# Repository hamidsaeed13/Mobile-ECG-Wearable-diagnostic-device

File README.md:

# Mobile ECG Project

### Supervisor:
-Prof. Dr. Shahid Khattak

### Team Members:
- Abdul Hameed
- M. Hamid Saeed
- Mujahid Haider

---

## Introduction:
This project aims to create a healthcare wearable Clinical Grade ECG device for continuous heart monitoring.

## Motivation:
- Existing ECG solutions are large and costly.
- Patients must be hospitalized, making it difficult to maintain long-term ECG logs.
- 24/7 ECG monitoring in remote areas is a challenge.

## Our Solution:
- 10-lead, 12-channel ECG diagnostic device.
- Bluetooth-enabled data transmission to smartphones for processing and log maintenance.
 
|  |  |

---

## Aims and Objectives:
- Signal acquisition and conditioning.
- Multiplexing and Bluetooth communication.
- Real-time ECG graph visualization.
- Log maintenance and record-sharing with cardiologists.

---

## System Block Diagram:

---
## Our Project:

---
## Filter Design:
- **Schematic**: 
  - R1 = 142.1KΩ
  - R2 = 120KΩ
  - C1 = C2 = 10nF
- **Design**: 
- **PCB**: 

---

## ADS1298:
- **Breakout Board**: 

- **PCB Layout**: 

---

## Android Application:
- Features:
  - Navigation menu with user details, doctor communication, and log maintenance.
  - 12-channel ECG view, Bluetooth connection, and real-time communication.
  - Options to find doctors and maintain a patient history.

---
## Database

---

## Working Schedule:
- Phase I (March 2016 - May 2016)
- Phase II (August 2016 - Onwards)

---

## Questions:
Feel free to reach out for further details.
*contact*: +92301 2216201
email: hamidsaeed13@gmail.com

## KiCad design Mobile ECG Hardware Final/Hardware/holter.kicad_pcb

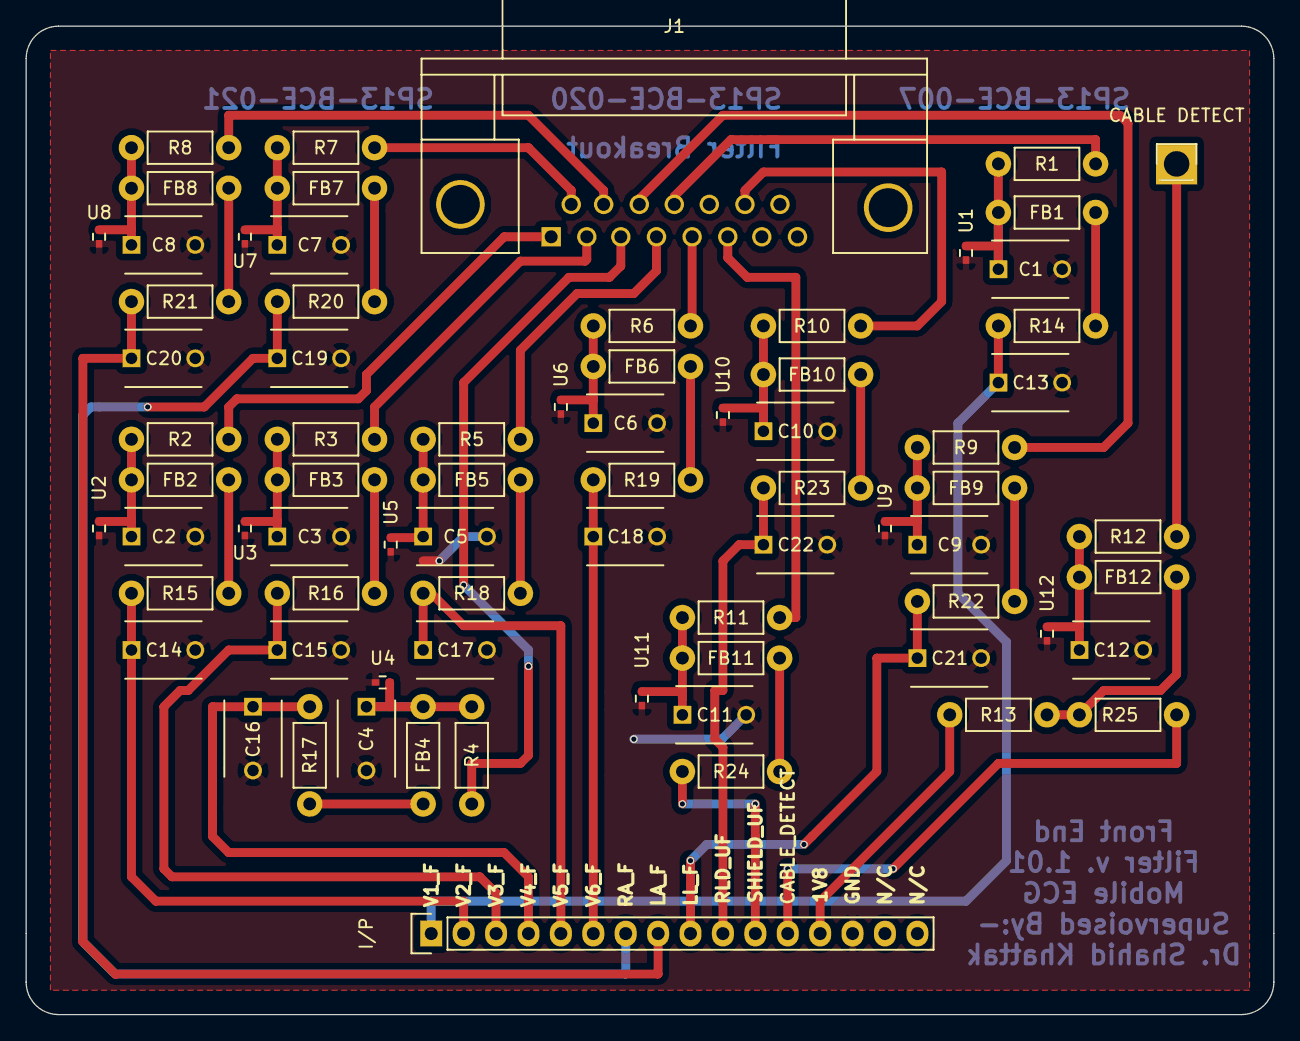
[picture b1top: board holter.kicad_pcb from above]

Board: 2 copper layers, 97.8 x 77.5 mm, 74 parts (0 on the bottom side), 50 nets.

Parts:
C1, C2, C3, C4, C5, C6, C7, C8, C9, C10, C11, C12, C13, C14, C15, C16, C17, C18, C19, C20, C21, C22: 47pF; C_Disc_D6_P5
CABLE DETECT: CONN_01X01; Pin_Header_Straight_1x01
FB1, FB2, FB3, FB4, FB5, FB6, FB7, FB8, FB9, FB10, FB11, FB12: FILTER; Resistor_Horizontal_RM7mm
I/P: CONN_01X16; Pin_Header_Straight_1x16
J1: DB15; DB15FC
R1, R2, R3, R4, R5, R6, R7, R8, R9, R10, R11, R12, R24: 470; Resistor_Horizontal_RM7mm
R13: 100k; Resistor_Horizontal_RM7mm
R14, R15, R16, R17, R18, R19, R20, R21, R22, R23: 10k; Resistor_Horizontal_RM7mm
R25: 47k; Resistor_Horizontal_RM7mm
U1, U2, U3, U4, U5, U6, U7, U8, U9, U10, U11, U12: TPD1E10B06DPYR; C_0402

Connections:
+1V8: I/P.13, R13.1
CABLE_DETECT: I/P.12, R25.2
DETECT: CABLE DETECT.1, R12.2
GND: C1.2, C2.2, C3.2, C4.2, C5.2, C6.2, C7.2, C8.2, C9.2, C10.2, C11.2, C12.2, C13.2, C14.2, C15.2, C16.2, C17.2, C18.2, C19.2, C20.2, C21.2, C22.2, I/P.14, U1.2, U2.2, U3.2, U4.2, U5.2, U6.2, U7.2, U8.2, U9.2, U10.2, U11.2, U12.2
LA: J1.10, R8.2
LA_F: C20.1, I/P.8, R21.1
LL: J1.11, R9.2
LL_F: C21.1, I/P.9, R22.1
unnamed: C1.1, FB1.1, R1.1, U1.1
unnamed: C2.1, FB2.1, R2.1, U2.1
unnamed: C3.1, FB3.1, R3.1, U3.1
unnamed: C4.1, FB4.1, R4.1, U4.1
unnamed: C5.1, FB5.1, R5.1, U5.1
unnamed: C6.1, FB6.1, R6.1, U6.1
unnamed: C7.1, FB7.1, R7.1, U7.1
unnamed: C8.1, FB8.1, R8.1, U8.1
unnamed: C9.1, FB9.1, R9.1, U9.1
unnamed: C10.1, FB10.1, R10.1, U10.1
unnamed: C11.1, FB11.1, R11.1, U11.1
unnamed: C12.1, FB12.2, R12.1, U12.1
unnamed: FB1.2, R14.2
unnamed: FB2.2, R15.2
unnamed: FB3.2, R16.2
unnamed: FB4.2, R17.2
unnamed: FB5.2, R18.2
unnamed: FB6.2, R19.2
unnamed: FB7.2, R20.2
unnamed: FB8.2, R21.2
unnamed: FB9.2, R22.2
unnamed: FB10.2, R23.2
unnamed: FB11.2, R24.2
unnamed: FB12.1, R13.2, R25.1
RA: J1.9, R7.2
RA_F: C19.1, I/P.7, R20.1
RLD: J1.14, R10.2
RLD_UF: C22.1, I/P.10, R23.1
SHIELD: J1.6, R11.2
SHIELD_UF: I/P.11, R24.1
V1: J1.12, R1.2
V1_F: C13.1, I/P.1, R14.1
V2: J1.1, R2.2
V2_F: C14.1, I/P.2, R15.1
V3: J1.2, R3.2
V3_F: C15.1, I/P.3, R16.1
V4: J1.3, R4.2
V4_F: C16.1, I/P.4, R17.1
V5: J1.4, R5.2
V5_F: C17.1, I/P.5, R18.1
V6: J1.5, R6.2
V6_F: C18.1, I/P.6, R19.1

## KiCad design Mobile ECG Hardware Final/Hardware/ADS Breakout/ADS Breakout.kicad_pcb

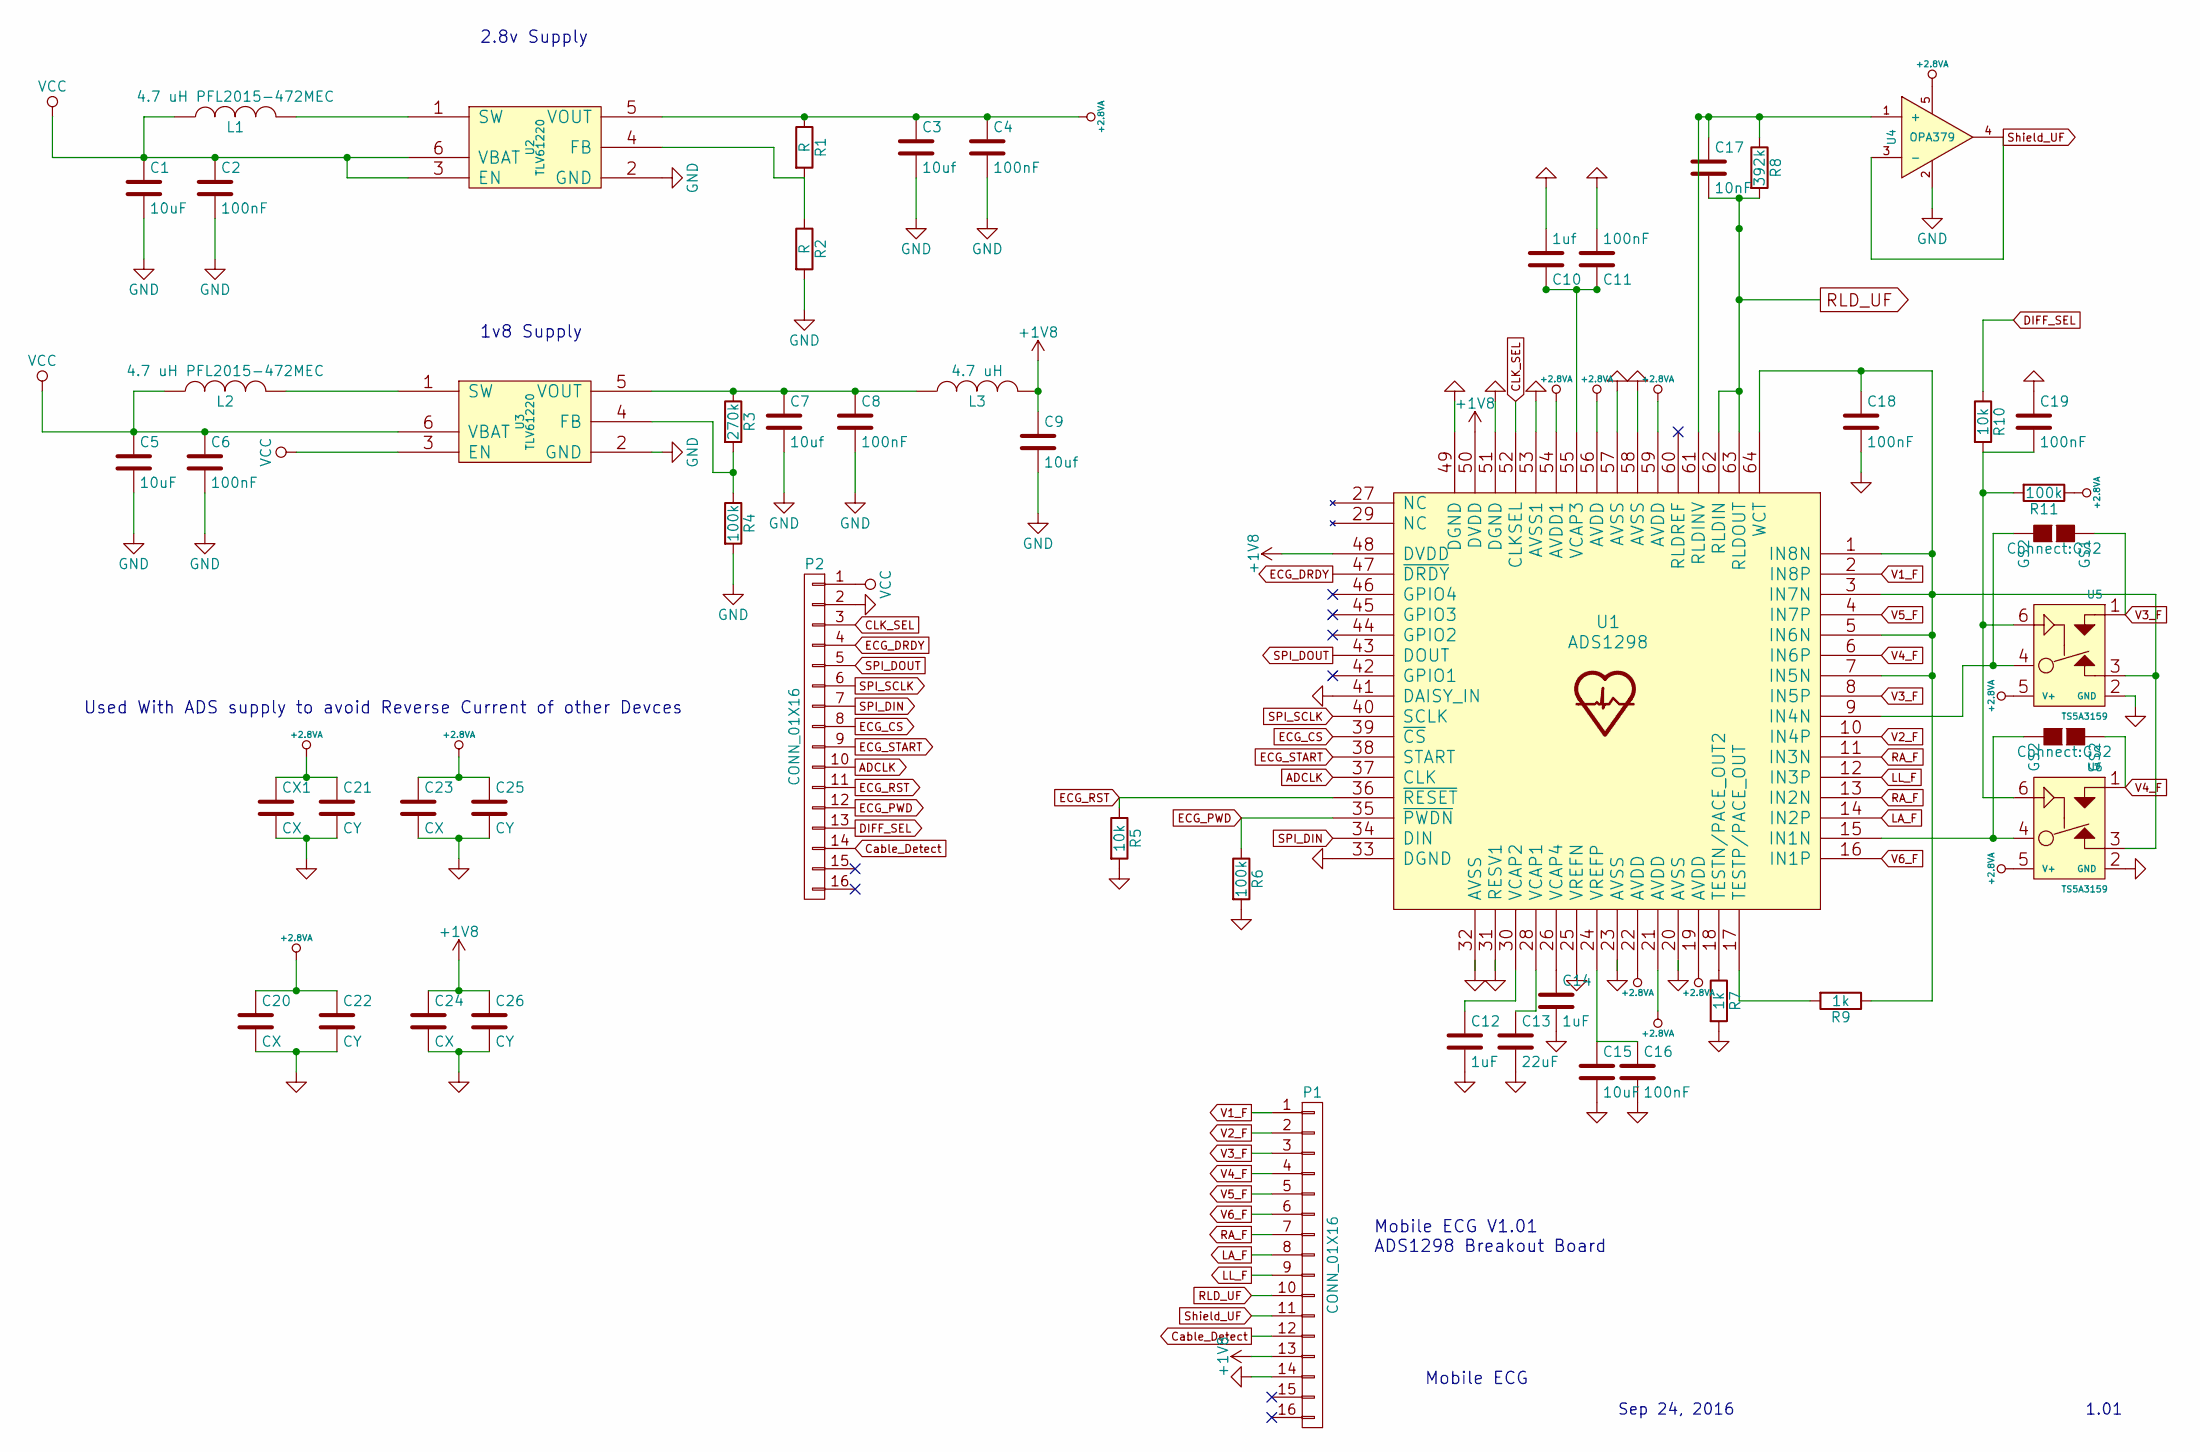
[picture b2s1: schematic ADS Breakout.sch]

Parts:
C1, C5, C15: 10uF; C_Disc_D3_P2.5
C2, C4, C6, C8, C11, C16, C18, C19: 100nF; C_Disc_D3_P2.5
C3, C7, C9: 10uf; C_Disc_D3_P2.5
C10: 1uf; C_Disc_D3_P2.5
C12, C14: 1uF; C_Disc_D3_P2.5
C13: 22uF; C_Disc_D3_P2.5
C17: 10nF; C_Disc_D3_P2.5
C20, C23, C24: CX; C_Disc_D3_P2.5
C21, C22, C25, C26: CY; C_Disc_D3_P2.5
CX1: CX; C_Disc_D3_P2.5
GS1, GS2: GS2
L1, L2: 4.7 uH PFL2015-472MEC; Resistor_Horizontal_RM7mm
L3: 4.7 uH; Resistor_Horizontal_RM7mm
P1, P2: CONN_01X16; Pin_Header_Straight_1x16
R1, R2: R; Resistor_Horizontal_RM7mm
R3: 270k; Resistor_Horizontal_RM7mm
R4, R6, R11: 100k; Resistor_Horizontal_RM7mm
R5, R10: 10k; Resistor_Horizontal_RM7mm
R7, R9: 1k; Resistor_Horizontal_RM7mm
R8: 392k; Resistor_Horizontal_RM7mm
U1: ADS1298; TQFP-64_10x10mm_Pitch0.5mm
U2, U3: TLV61220; SOT-23-6
U4: OPA379; SC-70-5
U5, U6: TS5A3159; SOT-23-6

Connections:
+1V8: C9.1, C24.1, C26.1, L3.2, P1.13, U1.48 (DVDD), U1.50 (DVDD); also elsewhere on the board
+2.8VA: C3.1, C4.1, C20.1, C21.1, C22.1, C23.1, C25.1, CX1.1, R1.1, R11.1, U1.19 (AVDD), U1.21 (AVDD), U1.22 (AVDD), U1.54 (AVDD1), U1.56 (AVDD), U1.59 (AVDD), U2.5 (VOUT), U4.5, U5.5 (V+), U6.5 (V+)
ADCLK: P2.10, U1.37 (CLK); also elsewhere on the board
CLK_SEL: P2.3, U1.52 (CLKSEL); also elsewhere on the board
DIFF_SEL: P2.13, R10.1; also elsewhere on the board
ECG_CS: P2.8, U1.39 (~CS); also elsewhere on the board
ECG_DRDY: P2.4, U1.47 (~DRDY); also elsewhere on the board
ECG_PWD: P2.12, R6.1, U1.35 (~PWDN); also elsewhere on the board
ECG_RST: P2.11, R5.1, U1.36 (~RESET); also elsewhere on the board
ECG_START: P2.9, U1.38 (START); also elsewhere on the board
GND: C1.2, C2.2, C3.2, C4.2, C5.2, C6.2, C7.2, C8.2, C9.2, C10.2, C11.2, C12.2, C13.2, C14.2, C15.2, C16.2, C18.2, C19.1, C20.2, C21.2, C22.2, C23.2, C24.2, C25.2, C26.2, CX1.2, P1.14, P2.2, R2.2, R4.2, R5.2, R6.2, R7.2, U1.20 (AVSS), U1.23 (AVSS), U1.25 (VREFN), U1.31 (RESV1), U1.32 (AVSS), U1.33 (DGND), U1.41 (DAISY_IN), U1.49 (DGND), U1.51 (DGND), U1.53 (AVSS1), U1.57 (AVSS), U1.58 (AVSS), U2.2 (GND), U3.2 (GND), U4.2, U5.2 (GND), U6.2 (GND); also elsewhere on the board
LA_F: P1.8, U1.14 (IN2P); also elsewhere on the board
LL_F: P1.9, U1.12 (IN3P); also elsewhere on the board
unnamed: C7.1, C8.1, L3.1, R3.1, U3.5 (VOUT)
unnamed: C10.1, C11.1, U1.55 (VCAP3)
unnamed: C12.1, U1.30 (VCAP2)
unnamed: C13.1, U1.28 (VCAP1)
unnamed: C14.1, U1.26 (VCAP4)
unnamed: C15.1, C16.1, U1.24 (VREFP)
unnamed: C17.1, R8.1, U1.61 (RLDINV), U4.1 (+)
unnamed: C18.1, R9.1, U1.1 (IN8N), U1.3 (IN7N), U1.5 (IN6N), U1.7 (IN5N), U1.64 (WCT), U5.3, U6.3
unnamed: C19.2, R10.2, R11.2, U5.6, U6.6
unnamed: GS1.2 (G2), U1.9 (IN4N), U5.4
unnamed: GS2.2 (G2), U1.15 (IN1N), U6.4
unnamed: L1.2, U2.1 (SW)
unnamed: L2.2, U3.1 (SW)
unnamed: P1.12, P2.14
unnamed: R1.2, R2.1, U2.4 (FB)
unnamed: R3.2, R4.1, U3.4 (FB)
unnamed: R7.1, U1.18 (TESTN/PACE_OUT2)
unnamed: R9.2, U1.17 (TESTP/PACE_OUT)
RA_F: P1.7, U1.11 (IN3N), U1.13 (IN2N); also elsewhere on the board
RLD_UF: C17.2, P1.10, R8.2, U1.62 (RLDIN), U1.63 (RLDOUT); also elsewhere on the board
SPI_DIN: P2.7, U1.34 (DIN); also elsewhere on the board
SPI_DOUT: P2.5, U1.43 (DOUT); also elsewhere on the board
SPI_SCLK: P2.6, U1.40 (SCLK); also elsewhere on the board
Shield_UF: P1.11, U4.3 (-), U4.4; also elsewhere on the board
V1_F: P1.1, U1.2 (IN8P); also elsewhere on the board
V2_F: P1.2, U1.10 (IN4P); also elsewhere on the board
V3_F: GS1.1 (G1), P1.3, U1.8 (IN5P), U5.1; also elsewhere on the board
V4_F: GS2.1 (G1), P1.4, U1.6 (IN6P), U6.1; also elsewhere on the board
V5_F: P1.5, U1.4 (IN7P); also elsewhere on the board
V6_F: P1.6, U1.16 (IN1P); also elsewhere on the board
VCC: C1.1, C2.1, C5.1, C6.1, L1.1, L2.1, P2.1, U2.3 (EN), U2.6 (VBAT), U3.3 (EN), U3.6 (VBAT); also elsewhere on the board

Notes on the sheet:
Mobile ECG V1.01 ADS1298 Breakout Board
Mobile ECG
Used With ADS supply to avoid Reverse Current of other Devces
2.8v Supply
1v8 Supply
Sep 24, 2016
1.01

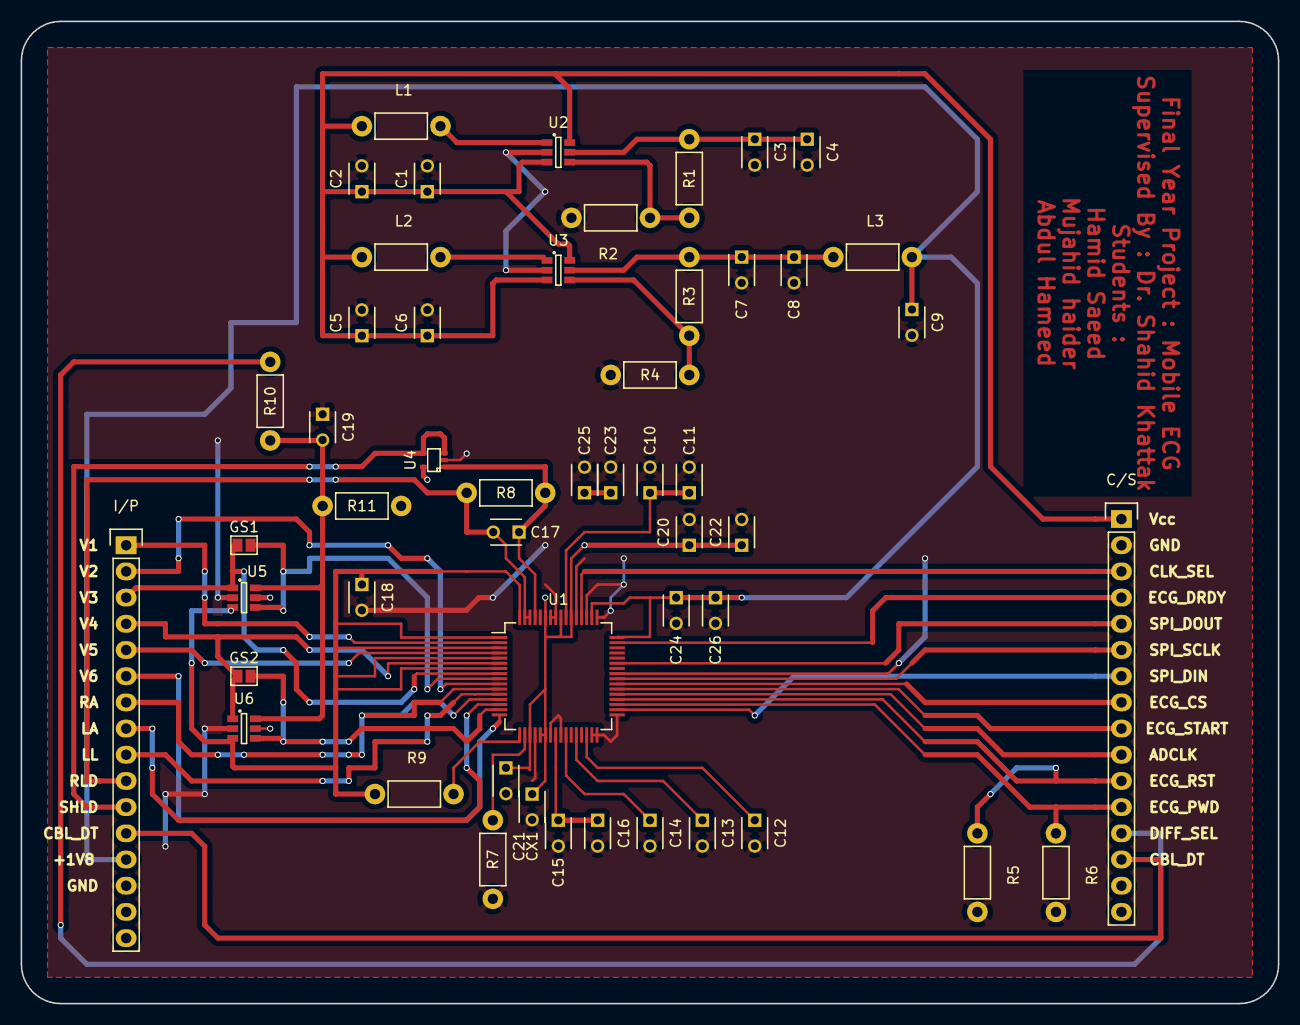
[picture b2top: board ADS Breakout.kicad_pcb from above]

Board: 2 copper layers, 121.9 x 95.2 mm, 51 parts (0 on the bottom side), 44 nets.

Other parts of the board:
C/S: CONN_01X16; Pin_Header_Straight_1x16
I/P: CONN_01X16; Pin_Header_Straight_1x16

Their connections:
+1V8: I/P.13; also elsewhere on the board
ADCLK: C/S.10; also elsewhere on the board
CLK_SEL: C/S.3; also elsewhere on the board
Cable_Detect: C/S.14, I/P.12
DIFF_SEL: C/S.13; also elsewhere on the board
ECG_CS: C/S.8; also elsewhere on the board
ECG_DRDY: C/S.4; also elsewhere on the board
ECG_PWD: C/S.12; also elsewhere on the board
ECG_RST: C/S.11; also elsewhere on the board
ECG_START: C/S.9; also elsewhere on the board
GND: C/S.2, I/P.14; also elsewhere on the board
LA_F: I/P.8; also elsewhere on the board
LL_F: I/P.9; also elsewhere on the board
RA_F: I/P.7; also elsewhere on the board
RLD_UF: I/P.10; also elsewhere on the board
SPI_DIN: C/S.7; also elsewhere on the board
SPI_DOUT: C/S.5; also elsewhere on the board
SPI_SCLK: C/S.6; also elsewhere on the board
Shield_UF: I/P.11; also elsewhere on the board
V1_F: I/P.1; also elsewhere on the board
V2_F: I/P.2; also elsewhere on the board
V3_F: I/P.3; also elsewhere on the board
V4_F: I/P.4; also elsewhere on the board
V5_F: I/P.5; also elsewhere on the board
V6_F: I/P.6; also elsewhere on the board
VCC: C/S.1; also elsewhere on the board

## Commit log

2024-09-23 init
2024-09-23 firmware
2024-09-23 Hardware
2024-09-23 Hardware PCB
2024-09-23 Final

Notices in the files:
Mobile ECG Hardware Final/Hardware/holter.kicad_pcb:
Licensed under Creative Commons Attribution-ShareAlike 4.0 International License
